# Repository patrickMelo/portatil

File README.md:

# Portatil

A "made-real" fantasy retro gaming console.

Portatil is a virtual machine based gaming console that runs RISC-V applications with custom system calls.

Runtimes can be easily ported to new targets by implementing specific drivers as kernel and engine code are target agnostic. Currently there are runtimes for Linux/SDL (mainly for development) and RaspiberryPi Pico (using RP2040 Zero from Waveshare).

## Virtual Machine Specifications

- CPU: RV32I instruction set (with custom fixed point math library).
- Memory: 32KB of RAM.
- Input: 8 digital inputs (left, right, up, down, a, b, x, y).
- Graphics: 160x120, 256 color framebuffer.
- Sound: 4 channel, 22KHz, 8-bit wave generator (sawtooth, square and triangle waves).
- 2D Engine: 4 layers, 256 sprites total, 128 entities on screen, basic physics simulation.
- Storage: FAT-32 formatted SD cards (read-only).

## Directory Structure

```sh
-- 3D Parts/    # 3D printable console shell
---- STL/       # exported parts for printing
-- Docs/        # hardware and software reference
-- Hardware/    # schematics and PCB design
-- Software/    # runtime and tools
---- Apps/      # demo application
---- Assets/    # runtime assets
---- Runtime/   # runtime code
------ Drivers/ # target specific code/drivers
------ States/  # high-level runtime code
---- SDK/       # C SDK
---- Targets/   # runtime targets
---- Tools/     # development tools
---- Utils/     # utilities
```

## TODO

There is still a lot of things to be done:
- Add actually usefull documentation to this repository;
- Create boilerplate code for new games;
- Write a tutorial on how to create your first game;
- Implement a Windows/SDL runtime;
- Add support for Windows based toolchains (to be able to compile games in Windows);
- Implement FAT-32 writing support;
- Add support for game saving;
- Add support for game thumbnails;

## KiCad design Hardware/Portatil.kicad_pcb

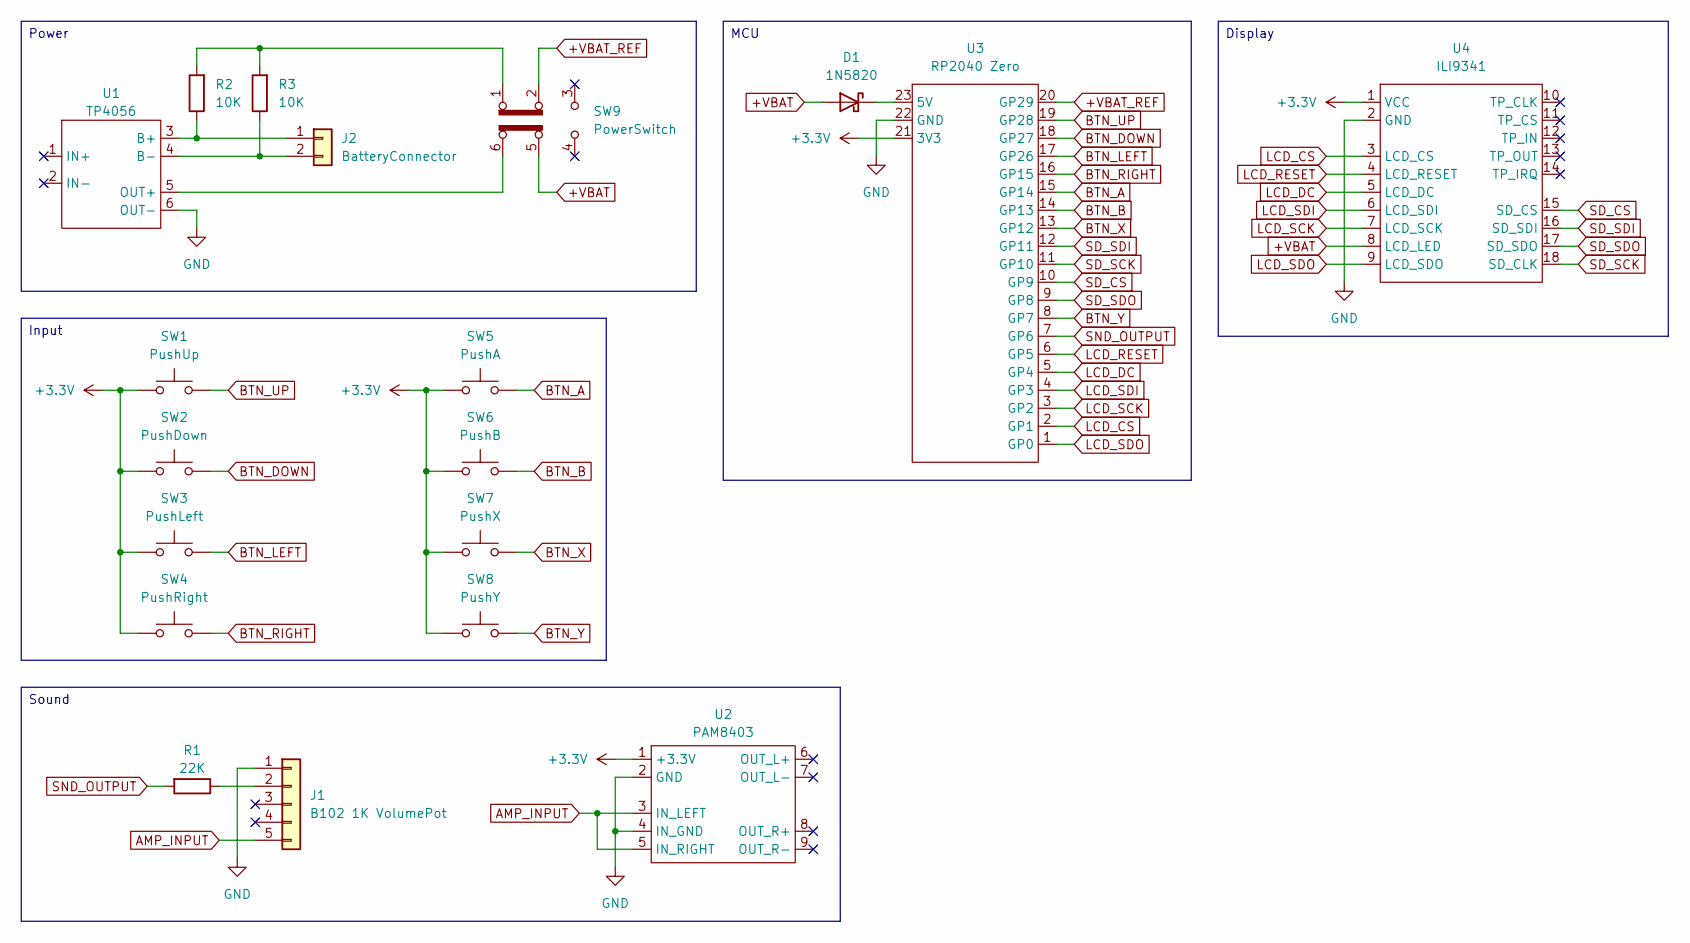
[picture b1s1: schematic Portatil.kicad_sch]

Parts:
D1: 1N5820; D_DO-35_SOD27_P7.62mm_Horizontal
J1: B102 1K VolumePot; Thumbwheel Potentiometer
J2: BatteryConnector; PinSocket_1x02_P2.54mm_Vertical
R1: 22K; R_Axial_DIN0207_L6.3mm_D2.5mm_P10.16mm_Horizontal
R2, R3: 10K; R_Axial_DIN0207_L6.3mm_D2.5mm_P10.16mm_Horizontal
SW1: PushUp; SW_PUSH_6mm
SW2: PushDown; SW_PUSH_6mm
SW3: PushLeft; SW_PUSH_6mm
SW4: PushRight; SW_PUSH_6mm
SW5: PushA; SW_PUSH_6mm
SW6: PushB; SW_PUSH_6mm
SW7: PushX; SW_PUSH_6mm
SW8: PushY; SW_PUSH_6mm
SW9: PowerSwitch; SW_CK_JS202011CQN_DPDT_Straight
U1: TP4056; TP4056 Module
U2: PAM8403; PAM8403 Module
U3: RP2040 Zero
U4: ILI9341; ILI9341 Module

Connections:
+3.3V: SW1.1, SW2.1, SW3.1, SW4.1, SW5.1, SW6.1, SW7.1, SW8.1, U2.1 (+3.3V), U3.21 (3V3), U4.1 (VCC)
+VBAT: D1.2 (A), SW9.5 (B), U4.8 (LCD_LED)
+VBAT_REF: SW9.2 (B), U3.20 (GP29)
AMP_INPUT: J1.5, U2.3 (IN_LEFT), U2.5 (IN_RIGHT)
BTN_A: SW5.2, U3.15 (GP14)
BTN_B: SW6.2, U3.14 (GP13)
BTN_DOWN: SW2.2, U3.18 (GP27)
BTN_LEFT: SW3.2, U3.17 (GP26)
BTN_RIGHT: SW4.2, U3.16 (GP15)
BTN_UP: SW1.2, U3.19 (GP28)
BTN_X: SW7.2, U3.13 (GP12)
BTN_Y: SW8.2, U3.8 (GP7)
GND: J1.1, U1.6 (OUT-), U2.2 (GND), U2.4 (IN_GND), U3.22 (GND), U4.2 (GND)
LCD_CS: U3.2 (GP1), U4.3 (LCD_CS)
LCD_DC: U3.5 (GP4), U4.5 (LCD_DC)
LCD_RESET: U3.6 (GP5), U4.4 (LCD_RESET)
LCD_SCK: U3.3 (GP2), U4.7 (LCD_SCK)
LCD_SDI: U3.4 (GP3), U4.6 (LCD_SDI)
LCD_SDO: U3.1 (GP0), U4.9 (LCD_SDO)
unnamed: D1.1 (K), U3.23 (5V)
unnamed: J1.2, R1.1
unnamed: J2.1, R2.1, U1.3 (B+)
unnamed: J2.2, R3.1, U1.4 (B-)
unnamed: R2.2, R3.2, SW9.1 (A)
unnamed: SW9.6 (C), U1.5 (OUT+)
SD_CS: U3.10 (GP9), U4.15 (SD_CS)
SD_SCK: U3.11 (GP10), U4.18 (SD_CLK)
SD_SDI: U3.12 (GP11), U4.16 (SD_SDI)
SD_SDO: U3.9 (GP8), U4.17 (SD_SDO)
SND_OUTPUT: R1.2, U3.7 (GP6)

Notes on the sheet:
Sound
MCU
Input
Display
Power

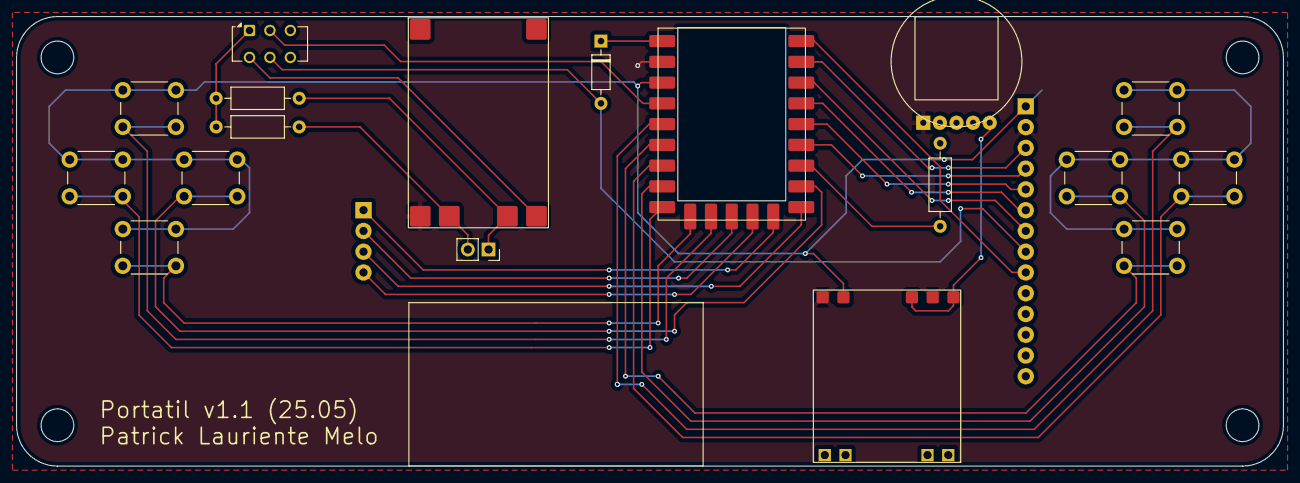
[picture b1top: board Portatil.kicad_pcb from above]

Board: 2 copper layers, 155.0 x 55.0 mm, 19 parts (1 on the bottom side), 30 nets.

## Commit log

2025-05-08 Initial release
2025-05-08 License added.
